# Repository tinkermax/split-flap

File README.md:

# Mechanical split-flap display
You can find full details and discussion on my [blog](https://tinkerwithtech.net/split-flap-display-brings-back-memories).

<br/>

This is an alternate electronics and firmware for David Kingsman's [Split-Flap Display](https://www.printables.com/model/69464-split-flap-display).

### Advantages
* Only one microprocessor is needed to drive a 12 character display, instead of the 13 microprocessors that would be required in the original design.
* Off-the-shelf ribbon cables are used between PCBs to reduce custom wiring.
* All components are through-hole mounted (i.e. no SMD).
* Overall, this should reduce assembly time and effort.

### Disadvantages
* PCBs are not mounted to the back of the display units but have their own mounting brackets. This approach is best suited for use in your own enclosure.
* A display of greater than 12 characters would require an additional controller board i.e. may not be as seamless as the original.
<br/><br/>

## Settings
### Turn on interactions and debugging over the USB serial port in [debug.h](include/debug.h):
DEBUG 1
<br/>
### Specify the number of Units (characters) in your display (4 -12) in [system.h](include/system.h):
unitCount 12
### Specify the network name of the display (useful if you have more than one display) in [system.h](include/system.h):
NETWORKNAME "splitflap"
<br/>
### Customise for each unit for your build. (Units are numbered left to right 0 - 11) in [unit.h](include/unit.h):
calOffsetUnit : an array of the offsets to move from hall sensor trigger to blank flap<br/>
FlapStep : an array containing the number of steps per stepper revolution (then divided by 45 flaps)
<br/>
### Password and localisation settings in [config.h](include/config.h):
WIFI_SSID "mySSID"<br/>
WIFI_PWD "myPassword"

MY_NTP_SERVER "au.pool.ntp.org" // Set the best fitting NTP server (pool) for your location<br/>
MY_TZ "AEST-10AEDT,M10.1.0,M4.1.0/3" // Set your time zone from https://github.com/nayarsystems/posix_tz_db/blob/master/zones.csv

WORDNIKAPIKEY "" // Get your private key from https://developer.wordnik.com/<br/>
MINWORDLEN 9 // Specify minimum word length to fetch from Wordnik<br/>
WORDUPDATESPERHOUR 1 // Set number of word updates from https://wordnik.com per hour. 0 will disable, else use an integer that results in an exact number of minutes btw updates i.e. 1,2,3,4,5,6,10,12,15,20,30 or 60
<br/><br/>
## Libraries
This project makes extensive use of two libraries:
* [FastAccelStepper](https://github.com/gin66/FastAccelStepper) by J.Kiemes
* [arduino-mcp23017](https://github.com/blemasle/arduino-mcp23017) by Bertrand Lemasle
<br/><br/>

## Connecting to the display
### There is a very basic web page served at http://splitflap.local/ to allow you to either enter text to display or fetch a random word from Wordnik 

<br/>

### There is also an API endpoint that you can POST to at http://splitflap.local/display, using a JSON payload in the body:

```json
{
    displaytext: "Display Text"
}
```

For example, you could use the request node within node-red:

<br/>

<br/><br/>

## PCBs
<br/>

Schematics for the Controller and Unit PCBs can be found under [schematics](schematics/).

Gerbers, Bill of materials and Kicad source files can be found under [PCBs](PCBs/).
<br/><br/>

## Brackets & unit frames 3D printing
PCB mounting brackets can be found on [Printables](https://www.printables.com/model/805853-split-flap-display).<br/> Also found there is my remixed unit frame. This is optional, as you could still use the original frames with the new electronics.
My unit frame requires an additional two M3\*L3\*D4 heat inserts for connecting to the adjacent unit.
<br/><br/>

## Enclosure (laser cut)

front<br/>
<br/>

rear<br/>
<br/>

Plywood (3mm) files for laser cutting are in [enclosure](enclosure/)
<br/><br/>

## Licensing
Copyright (c) 2024 Malcolm Yeoman.<br/>

Electronics is released under [CERN-OHL-P (Permissive) V2](https://ohwr.org/cern_ohl_p_v2.pdf).<br/>
Firmware is released under the [MIT License](http://opensource.org/licenses/MIT).<br/>
Documentation is licensed under a [Creative Commons Attribution 4.0 International License](http://creativecommons.org/licenses/by-sa/4.0/).

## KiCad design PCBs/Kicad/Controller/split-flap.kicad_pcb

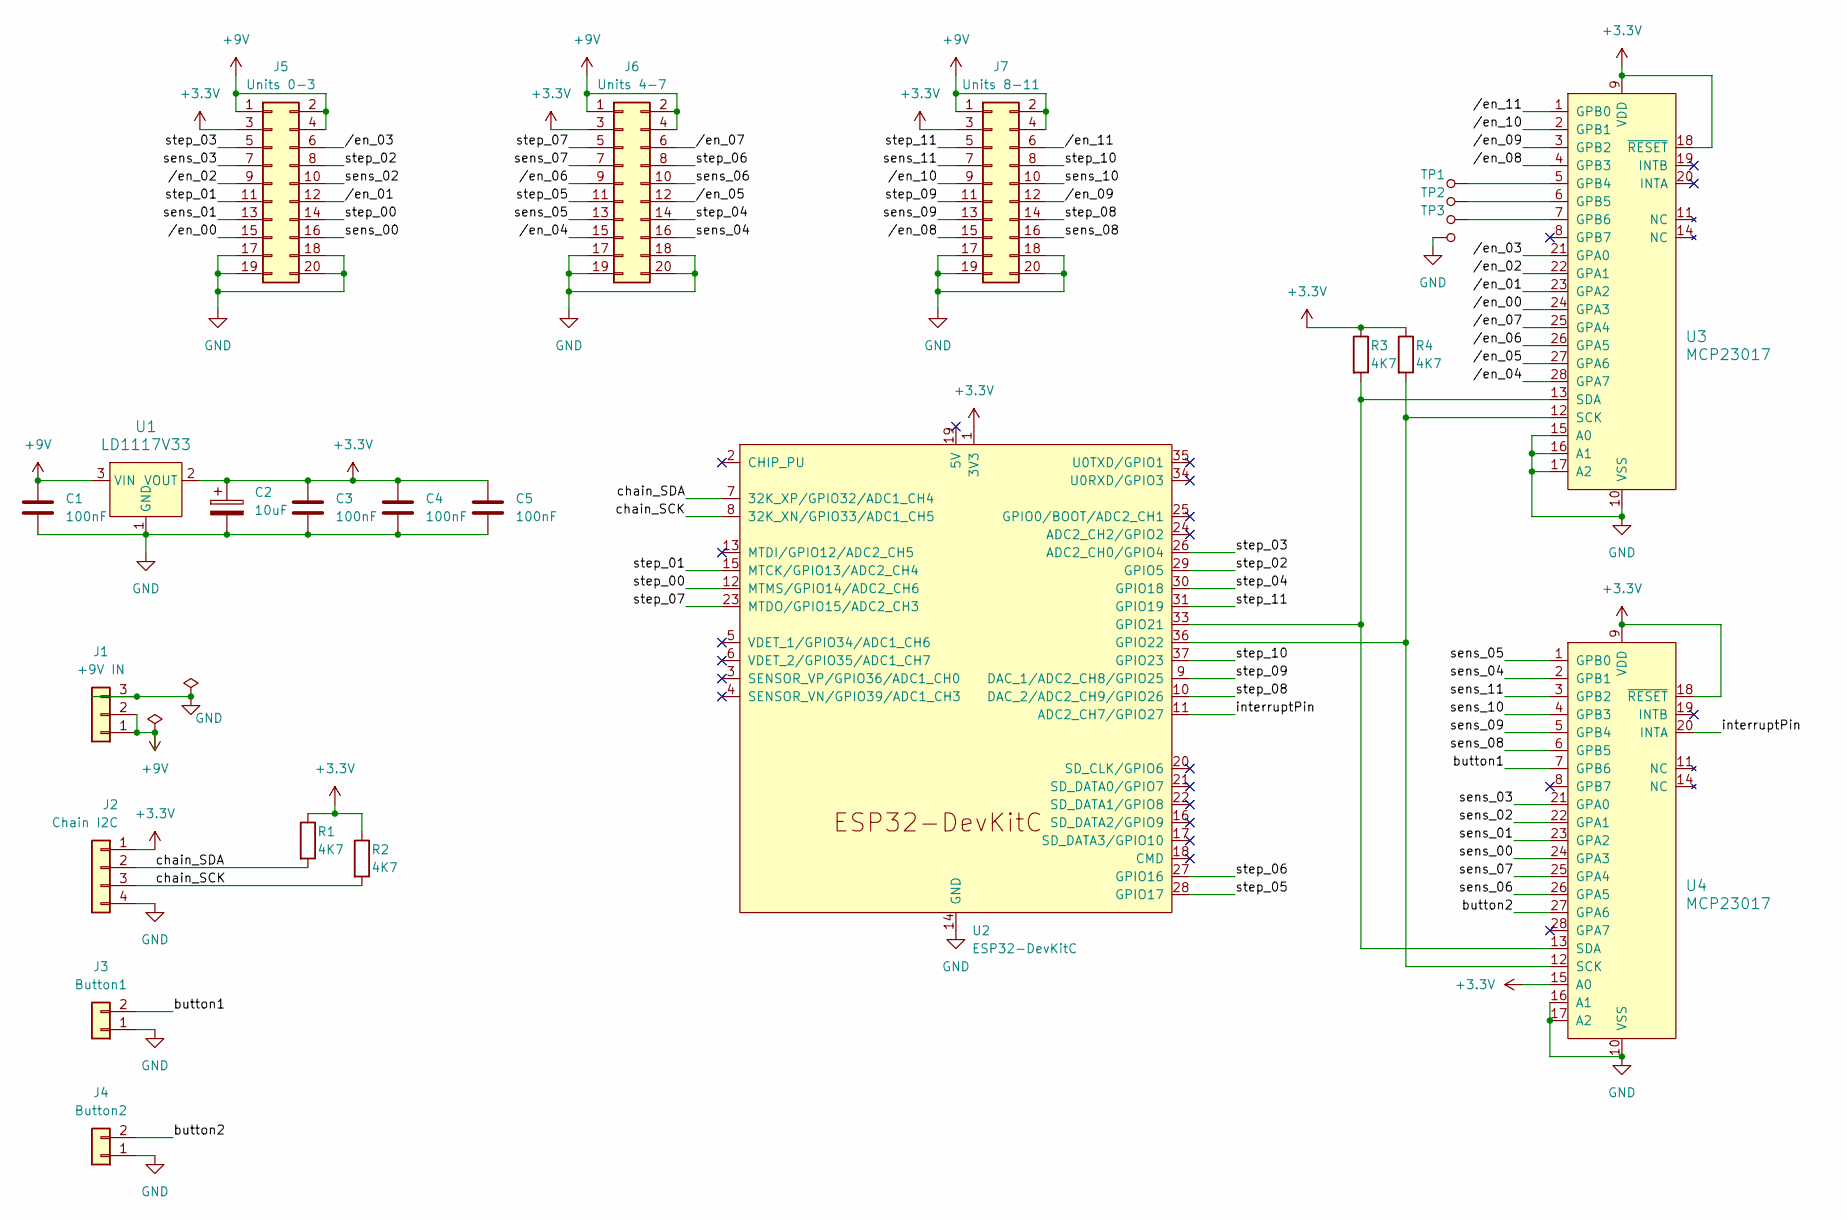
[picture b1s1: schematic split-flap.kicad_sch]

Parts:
C1, C3, C4, C5: 100nF; C_Disc_D3.4mm_W2.1mm_P2.50mm
C2: 10uF; CP_Radial_D5.0mm_P2.00mm
J1: +9V IN; TerminalBlock_TE_282834-3_1x03_P2.54mm_Horizontal
J2: Chain I2C; PinSocket_1x04_P2.54mm_Vertical
J3: Button1; PinSocket_1x02_P2.54mm_Vertical
J4: Button2; PinSocket_1x02_P2.54mm_Vertical
J5: Units 0-3; IDC-Header_2x10_P2.54mm_Vertical
J6: Units 4-7; IDC-Header_2x10_P2.54mm_Vertical
J7: Units 8-11; IDC-Header_2x10_P2.54mm_Vertical
R1, R2, R3, R4: 4K7; R_Axial_DIN0207_L6.3mm_D2.5mm_P7.62mm_Horizontal
TP1, TP2, TP3, TP4: 5000; Test_Point_D1.02mm; MPN 5000; Digi-Key_PN 36-5000-ND
U1: LD1117V33; TO-220-3; MPN LD1117V33; Digi-Key_PN 497-1491-5-ND
U2: ESP32-DevKitC
U3, U4: MCP23017; DIP-28_W7.62mm; MPN MCP23017-E/SP; Digi-Key_PN MCP23017-E/SP-ND

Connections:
+3.3V: C2.1, C3.1, C4.1, C5.1, J2.1, J5.3, J6.3, J7.3, R1.1, R2.1, R3.1, R4.1, U1.2 (VOUT), U2.1 (3V3), U3.9 (VDD), U3.18 (~RESET), U4.9 (VDD), U4.15 (A0), U4.18 (~RESET)
+9V: C1.1, J1.1, J1.2, J5.1, J5.2, J5.4, J6.1, J6.2, J6.4, J7.1, J7.2, J7.4, U1.3 (VIN)
/button1: J3.2, U4.7 (GPB6)
/button2: J4.2, U4.27 (GPA6)
/chain_SCK: J2.3, R2.2, U2.8 (32K_XN/GPIO33/ADC1_CH5)
/chain_SDA: J2.2, R1.2, U2.7 (32K_XP/GPIO32/ADC1_CH4)
/interruptPin: U2.11 (ADC2_CH7/GPIO27), U4.20 (INTA)
/sens_00: J5.16, U4.24 (GPA3)
/sens_01: J5.13, U4.23 (GPA2)
/sens_02: J5.10, U4.22 (GPA1)
/sens_03: J5.7, U4.21 (GPA0)
/sens_04: J6.16, U4.2 (GPB1)
/sens_05: J6.13, U4.1 (GPB0)
/sens_06: J6.10, U4.26 (GPA5)
/sens_07: J6.7, U4.25 (GPA4)
/sens_08: J7.16, U4.6 (GPB5)
/sens_09: J7.13, U4.5 (GPB4)
/sens_10: J7.10, U4.4 (GPB3)
/sens_11: J7.7, U4.3 (GPB2)
/step_00: J5.14, U2.12 (MTMS/GPIO14/ADC2_CH6)
/step_01: J5.11, U2.15 (MTCK/GPIO13/ADC2_CH4)
/step_02: J5.8, U2.29 (GPIO5)
/step_03: J5.5, U2.26 (ADC2_CH0/GPIO4)
/step_04: J6.14, U2.30 (GPIO18)
/step_05: J6.11, U2.28 (GPIO17)
/step_06: J6.8, U2.27 (GPIO16)
/step_07: J6.5, U2.23 (MTDO/GPIO15/ADC2_CH3)
/step_08: J7.14, U2.10 (DAC_2/ADC2_CH9/GPIO26)
/step_09: J7.11, U2.9 (DAC_1/ADC2_CH8/GPIO25)
/step_10: J7.8, U2.37 (GPIO23)
/step_11: J7.5, U2.31 (GPIO19)
//en_00: J5.15, U3.24 (GPA3)
//en_01: J5.12, U3.23 (GPA2)
//en_02: J5.9, U3.22 (GPA1)
//en_03: J5.6, U3.21 (GPA0)
//en_04: J6.15, U3.28 (GPA7)
//en_05: J6.12, U3.27 (GPA6)
//en_06: J6.9, U3.26 (GPA5)
//en_07: J6.6, U3.25 (GPA4)
//en_08: J7.15, U3.4 (GPB3)
//en_09: J7.12, U3.3 (GPB2)
//en_10: J7.9, U3.2 (GPB1)
//en_11: J7.6, U3.1 (GPB0)
GND: C1.2, C2.2, C3.2, C4.2, C5.2, J1.3, J2.4, J3.1, J4.1, J5.17, J5.18, J5.19, J5.20, J6.17, J6.18, J6.19, J6.20, J7.17, J7.18, J7.19, J7.20, TP4.1, U1.1 (GND), U2.14 (GND), U2.32 (GND), U2.38 (GND), U3.10 (VSS), U3.15 (A0), U3.16 (A1), U3.17 (A2), U4.10 (VSS), U4.16 (A1), U4.17 (A2)
unnamed: R3.2, U2.33 (GPIO21), U3.13 (SDA), U4.13 (SDA)
unnamed: R4.2, U2.36 (GPIO22), U3.12 (SCK), U4.12 (SCK)
unnamed: TP1.1, U3.5 (GPB4)
unnamed: TP2.1, U3.6 (GPB5)
unnamed: TP3.1, U3.7 (GPB6)

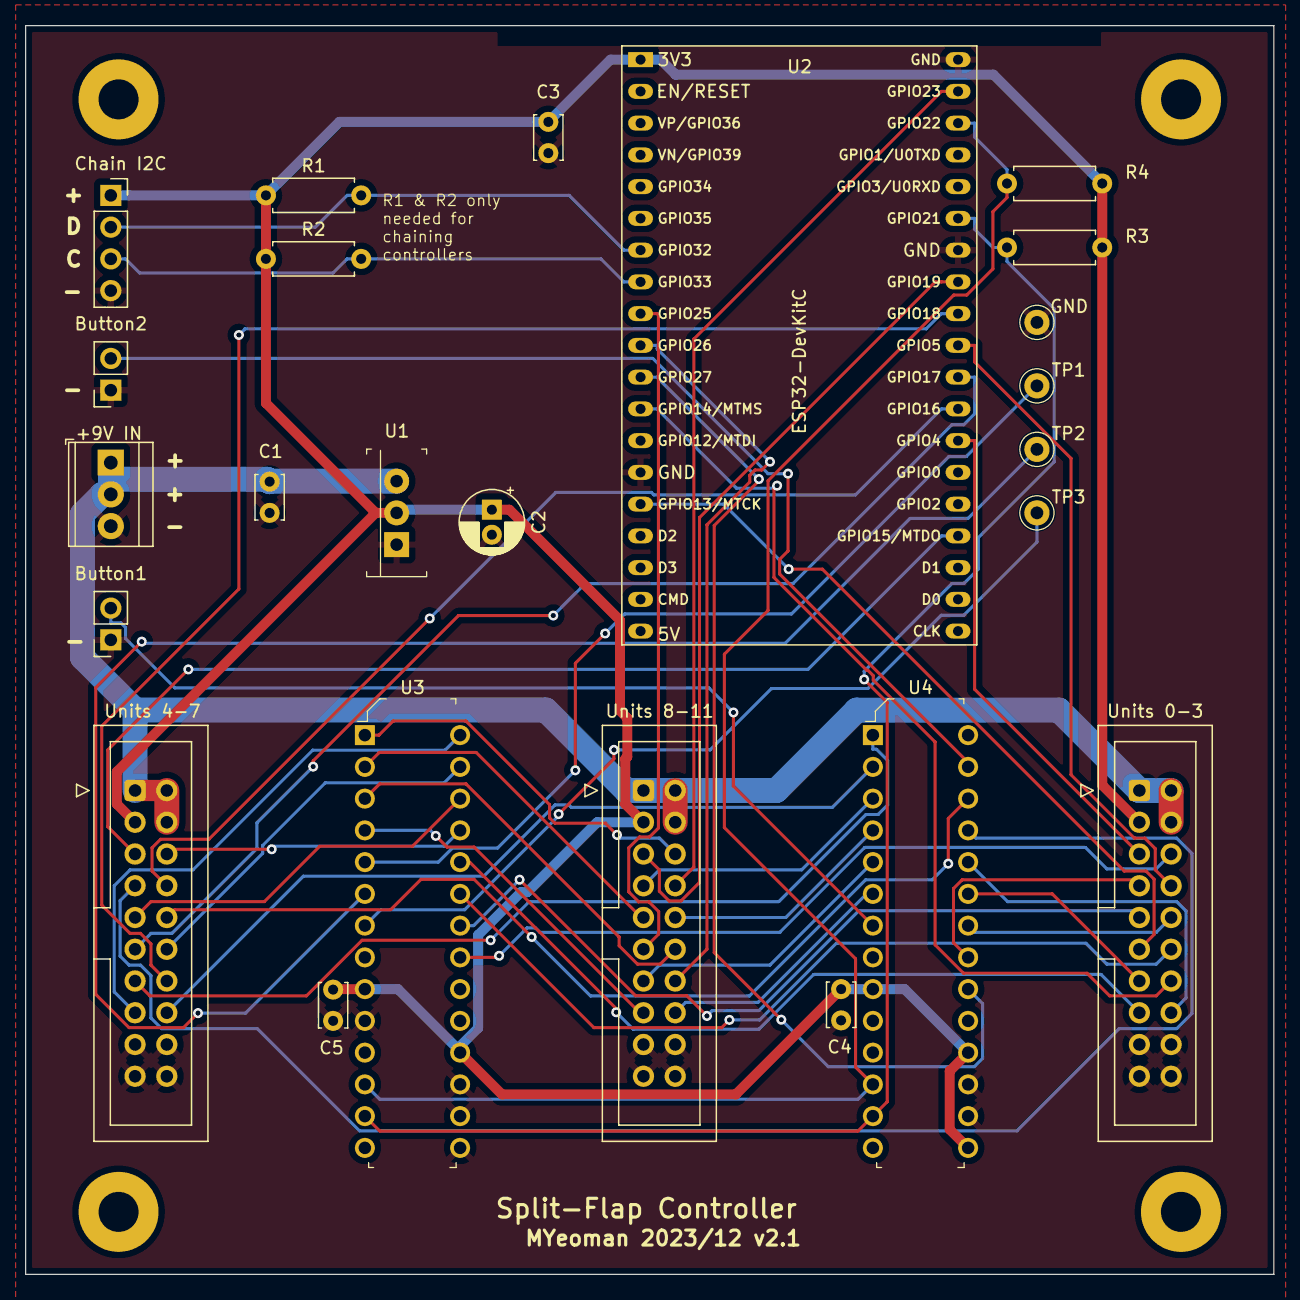
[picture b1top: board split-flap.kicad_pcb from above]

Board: 2 copper layers, 99.9 x 99.9 mm, 28 parts (0 on the bottom side), 49 nets.

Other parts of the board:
REF1, REF2, REF3, REF4: MountingHole_3.2mm_M3_Pad

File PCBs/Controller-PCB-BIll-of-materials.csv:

Reference,Value,Footprint,Qty
"C1,C3,C4,C5",100nF,Capacitor_THT:C_Disc_D3.4mm_W2.1mm_P2.50mm,4
C2,10uF,Capacitor_THT:CP_Radial_D5.0mm_P2.00mm,1
J1,+9V IN,TerminalBlock_TE-Connectivity:TerminalBlock_TE_282834-3_1x03_P2.54mm_Horizontal,1
J2,Chain I2C,Connector_PinSocket_2.54mm:PinSocket_1x04_P2.54mm_Vertical,1
J3,Button1,Connector_PinSocket_2.54mm:PinSocket_1x02_P2.54mm_Vertical,1
J4,Button2,Connector_PinSocket_2.54mm:PinSocket_1x02_P2.54mm_Vertical,1
J5,Units 0-3,Connector_IDC:IDC-Header_2x10_P2.54mm_Vertical,1
J6,Units 4-7,Connector_IDC:IDC-Header_2x10_P2.54mm_Vertical,1
J7,Units 8-11,Connector_IDC:IDC-Header_2x10_P2.54mm_Vertical,1
"R1,R2,R3,R4",4K7,Resistor_THT:R_Axial_DIN0207_L6.3mm_D2.5mm_P7.62mm_Horizontal,4
"TP1,TP2,TP3,TP4",5000,digikey-footprints:Test_Point_D1.02mm,4
U1,LD1117V33,digikey-footprints:TO-220-3,1
U2,ESP32-DevKitC,PCM_Espressif:ESP32-DevKitC,1
"U3,U4",MCP23017,digikey-footprints:DIP-28_W7.62mm,2

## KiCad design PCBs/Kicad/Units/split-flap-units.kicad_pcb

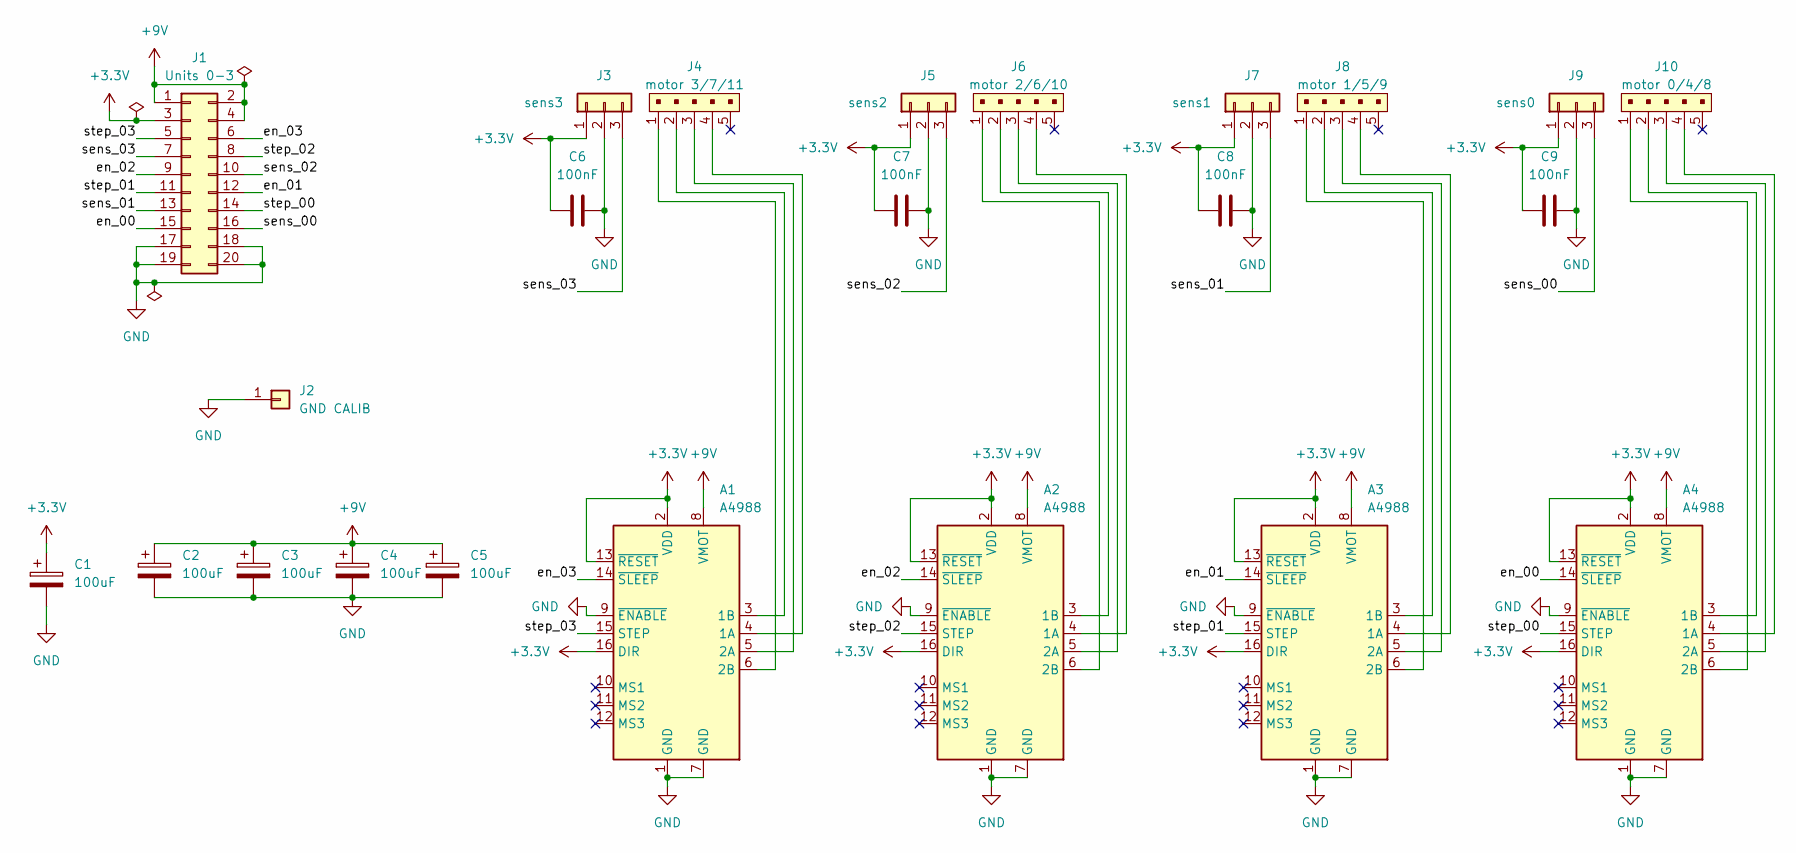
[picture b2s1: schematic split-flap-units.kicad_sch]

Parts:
A1, A2, A3, A4: A4988; A4988_Stepper_Module
C1, C2, C3, C4, C5: 100uF; CP_Radial_D6.3mm_P2.50mm
C6, C7, C8, C9: 100nF; C_Disc_D3.4mm_W2.1mm_P2.50mm
J1: Units 0-3; IDC-Header_2x10_P2.54mm_Vertical
J2: GND CALIB; PinHeader_1x01_P2.54mm_Vertical
J3: sens3; PinSocket_1x03_P2.54mm_Vertical
J4: motor 3/7/11; JST_XH_B5B-XH-A_1x05_P2.50mm_Vertical; MPN B5B-XH-A(LF)(SN); Digi-Key_PN 455-2270-ND
J5: sens2; PinSocket_1x03_P2.54mm_Vertical
J6: motor 2/6/10; JST_XH_B5B-XH-A_1x05_P2.50mm_Vertical; MPN B5B-XH-A(LF)(SN); Digi-Key_PN 455-2270-ND
J7: sens1; PinSocket_1x03_P2.54mm_Vertical
J8: motor 1/5/9; JST_XH_B5B-XH-A_1x05_P2.50mm_Vertical; MPN B5B-XH-A(LF)(SN); Digi-Key_PN 455-2270-ND
J9: sens0; PinSocket_1x03_P2.54mm_Vertical
J10: motor 0/4/8; JST_XH_B5B-XH-A_1x05_P2.50mm_Vertical; MPN B5B-XH-A(LF)(SN); Digi-Key_PN 455-2270-ND

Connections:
+3.3V: A1.2 (VDD), A1.13 (~RESET), A1.16 (DIR), A2.2 (VDD), A2.13 (~RESET), A2.16 (DIR), A3.2 (VDD), A3.13 (~RESET), A3.16 (DIR), A4.2 (VDD), A4.13 (~RESET), A4.16 (DIR), C1.1, C6.1, C7.1, C8.1, C9.1, J1.3, J3.1, J5.1, J7.1, J9.1
+9V: A1.8 (VMOT), A2.8 (VMOT), A3.8 (VMOT), A4.8 (VMOT), C2.1, C3.1, C4.1, C5.1, J1.1, J1.2, J1.4
/en_00: A4.14 (~SLEEP), J1.15
/en_01: A3.14 (~SLEEP), J1.12
/en_02: A2.14 (~SLEEP), J1.9
/en_03: A1.14 (~SLEEP), J1.6
/sens_00: J1.16, J9.3
/sens_01: J1.13, J7.3
/sens_02: J1.10, J5.3
/sens_03: J1.7, J3.3
/step_00: A4.15 (STEP), J1.14
/step_01: A3.15 (STEP), J1.11
/step_02: A2.15 (STEP), J1.8
/step_03: A1.15 (STEP), J1.5
GND: A1.1 (GND), A1.7 (GND), A1.9 (~ENABLE), A2.1 (GND), A2.7 (GND), A2.9 (~ENABLE), A3.1 (GND), A3.7 (GND), A3.9 (~ENABLE), A4.1 (GND), A4.7 (GND), A4.9 (~ENABLE), C1.2, C2.2, C3.2, C4.2, C5.2, C6.2, C7.2, C8.2, C9.2, J1.17, J1.18, J1.19, J1.20, J2.1, J3.2, J5.2, J7.2, J9.2
unnamed: A1.4 (1A), J4.4
unnamed: A1.3 (1B), J4.2
unnamed: A1.5 (2A), J4.3
unnamed: A1.6 (2B), J4.1
unnamed: A2.4 (1A), J6.4
unnamed: A2.3 (1B), J6.2
unnamed: A2.5 (2A), J6.3
unnamed: A2.6 (2B), J6.1
unnamed: A3.4 (1A), J8.4
unnamed: A3.3 (1B), J8.2
unnamed: A3.5 (2A), J8.3
unnamed: A3.6 (2B), J8.1
unnamed: A4.4 (1A), J10.4
unnamed: A4.3 (1B), J10.2
unnamed: A4.5 (2A), J10.3
unnamed: A4.6 (2B), J10.1

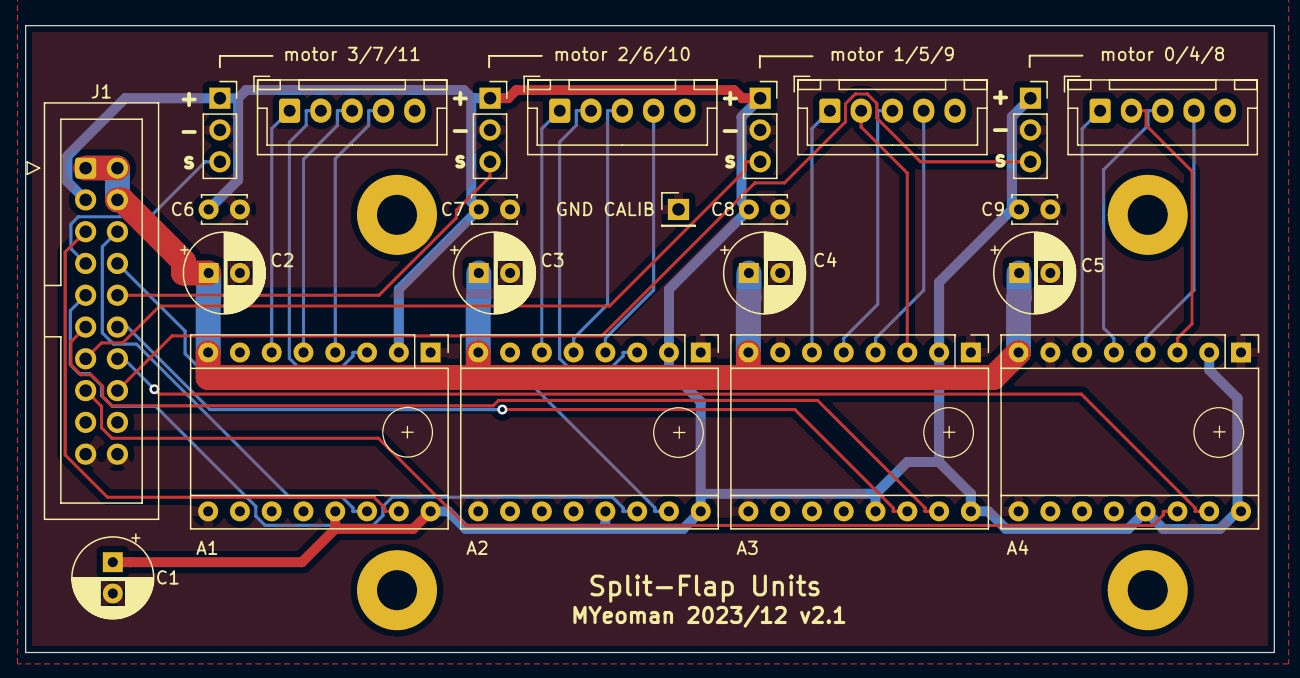
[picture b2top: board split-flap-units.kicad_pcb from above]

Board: 2 copper layers, 99.8 x 50.1 mm, 27 parts (0 on the bottom side), 31 nets.

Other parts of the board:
REF1, REF2, REF3, REF4: MountingHole_3.2mm_M3_Pad

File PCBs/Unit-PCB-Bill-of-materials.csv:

"Reference","Value","Datasheet","Footprint","Qty","DNP"
"A1,A2,A3,A4","A4988","https://www.pololu.com/product/2980/pictures","User:A4988_Stepper_Module","4",""
"C1,C2,C3,C4,C5","100uF","~","Capacitor_THT:CP_Radial_D6.3mm_P2.50mm","5",""
"C6,C7,C8,C9","100nF","~","Capacitor_THT:C_Disc_D3.4mm_W2.1mm_P2.50mm","4",""
"J1","Units 0-3","~","Connector_IDC:IDC-Header_2x10_P2.54mm_Vertical","1",""
"J2","GND CALIB","~","Connector_PinHeader_2.54mm:PinHeader_1x01_P2.54mm_Vertical","1",""
"J3","sens3","~","Connector_PinSocket_2.54mm:PinSocket_1x03_P2.54mm_Vertical","1",""
"J4","motor 3/7/11","http://www.jst-mfg.com/product/pdf/eng/eXH.pdf","Connector_JST:JST_XH_B5B-XH-A_1x05_P2.50mm_Vertical","1",""
"J5","sens2","~","Connector_PinSocket_2.54mm:PinSocket_1x03_P2.54mm_Vertical","1",""
"J6","motor 2/6/10","http://www.jst-mfg.com/product/pdf/eng/eXH.pdf","Connector_JST:JST_XH_B5B-XH-A_1x05_P2.50mm_Vertical","1",""
"J7","sens1","~","Connector_PinSocket_2.54mm:PinSocket_1x03_P2.54mm_Vertical","1",""
"J8","motor 1/5/9","http://www.jst-mfg.com/product/pdf/eng/eXH.pdf","Connector_JST:JST_XH_B5B-XH-A_1x05_P2.50mm_Vertical","1",""
"J9","sens0","~","Connector_PinSocket_2.54mm:PinSocket_1x03_P2.54mm_Vertical","1",""
"J10","motor 0/4/8","http://www.jst-mfg.com/product/pdf/eng/eXH.pdf","Connector_JST:JST_XH_B5B-XH-A_1x05_P2.50mm_Vertical","1",""

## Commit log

2024-03-28 first public commit
2024-04-30 Wordnik had modified their excludePartOfSpeech API
2024-09-18 Improve recovery from error; add NETWORKNAME config
2024-10-14 prevent initial word fetch when WORDUPDATESPERHOUR set to 0
